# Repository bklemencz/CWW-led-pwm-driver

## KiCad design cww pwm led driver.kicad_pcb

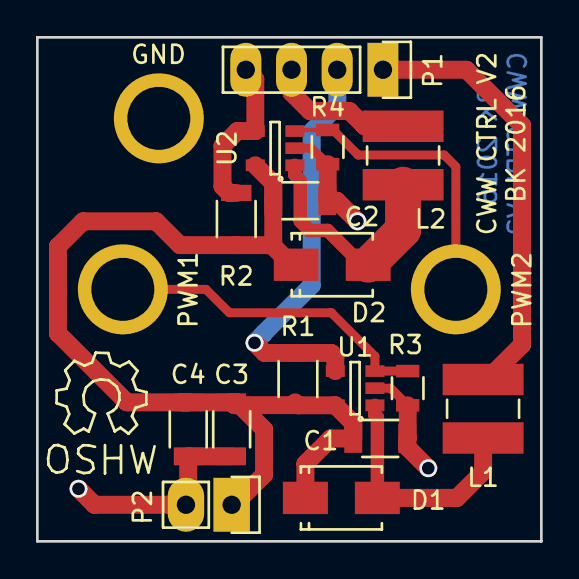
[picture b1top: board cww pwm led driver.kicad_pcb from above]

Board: 2 copper layers, 28.0 x 28.0 mm, 19 parts (0 on the bottom side), 10 nets.

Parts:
C1, C2: 10uF 50V; C_1206
C3, C4: 10uF; C_1206
D1, D2: SS14; SMA_Standard
GND: GND; MountingHole_3.5mm_5mm_Pad
L1, L2: 47uH; IND_SMD_CD43
P1: CONN_01X04; Pin_Header_Straight_1x04
P2: CONN_01X02; Pin_Header_Straight_1x02
PWM1: PWM1; MountingHole_3.5mm_5mm_Pad
PWM2: PWM2; MountingHole_3.5mm_5mm_Pad
R1, R2: 0R39; R_1206
R3, R4: 10k; R_0805
U1, U2: BP1360; SOT-23-5

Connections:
/OUT1_N: L1.1, P1.1
/OUT1_P: P1.2, R1.1, U1.4
/OUT2_N: L2.1, P1.3
/OUT2_P: P1.4, R2.1, U2.4
/VIN: C1.1, C2.1, C3.1, C4.1, D1.1, D2.1, P2.1, R1.2, R2.2, U1.5, U2.5
GND: C1.2, C2.2, C3.2, C4.2, GND.1, P2.2, R3.2, R4.2, U1.2, U2.2
unnamed: D1.2, L1.2, U1.1
unnamed: D2.2, L2.2, U2.1
unnamed: PWM1.1, R3.1, U1.3
unnamed: PWM2.1, R4.1, U2.3

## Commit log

2016-03-13 :neckbeard: Added .gitattributes & .gitignore files
2016-03-13 initial
